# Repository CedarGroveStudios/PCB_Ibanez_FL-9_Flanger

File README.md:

## PCB_Ibanez_FL-9_Flanger
 An as-built schematic, PCB layout, and service guide to help with the repair of the Ibanez FL-9 Flanger guitar pedal.
 
 [FL9 Flanger Repair Blog (.pdf)](https://github.com/CedarGroveStudios/PCB_Ibanez_FL-9_Flanger/blob/main/docs/repair_blog/Ibanez_FL9_Flanger_Repair_Blog.pdf)

 [New Service Guide (Adafruit Learning System)](https://learn.adafruit.com/u/CGrover/pages/ibanez-fl9-service-guide)

 [New Service Guide (.pdf)](https://github.com/CedarGroveStudios/PCB_Ibanez_FL-9_Flanger/blob/main/docs/new_service_guide/Ibanez_FL9_Service_Guide.pdf)
 
 [KiCAD PCB Design Folder](https://github.com/CedarGroveStudios/PCB_Ibanez_FL-9_Flanger/tree/main/PCB)

 NOTE: The reverse-engineered PCB design was only used for relative component location -- the design is untested.

A thank you to [Mystic Effects Co](https://mysticeffectsco.com) for a helpful and inspiring FL9 capacitor replacement blog post. Also to Panasonic for continuing to maintain on-line datasheets for the bucket-brigade delay and clock driver chip set. Let's not forget how great it is that DigiKey still stocks fresh through-hole capacitors in their produce aisle.

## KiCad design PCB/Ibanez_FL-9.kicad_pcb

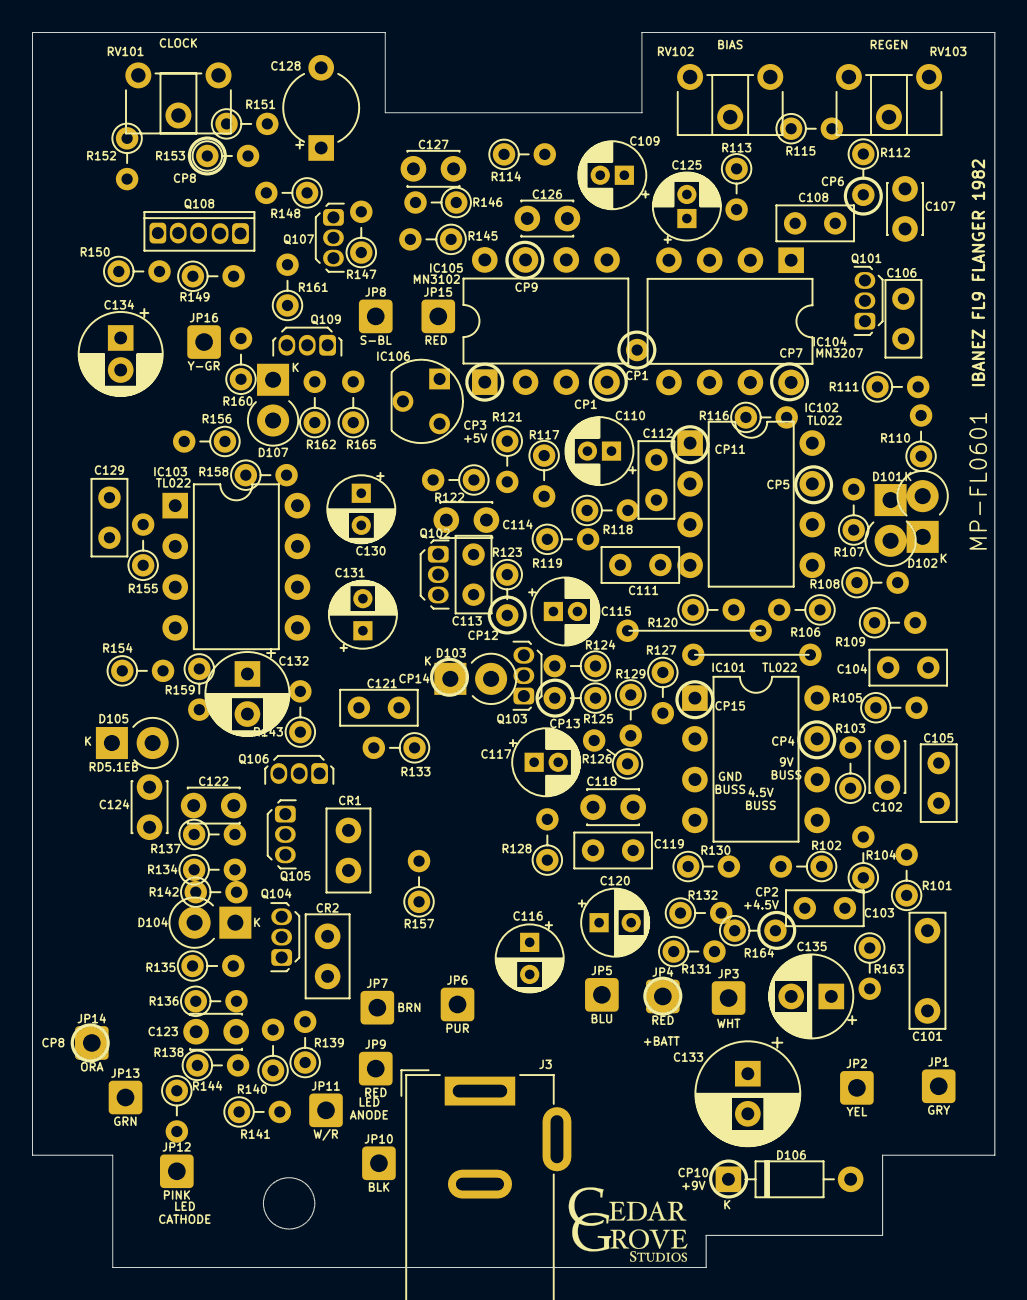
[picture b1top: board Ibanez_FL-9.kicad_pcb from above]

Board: 2 copper layers, 60.0 x 77.0 mm, 144 parts (0 on the bottom side), 77 nets, no tracks yet.

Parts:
C101: 0.047uf FILM; C_Rect_L7.0mm_W2.0mm_P5.00mm
C102, C118: 100pf CER; C_Disc_D3.0mm_W2.0mm_P2.50mm
C103: 0.022uf FILM; C_Rect_L4.6mm_W2.0mm_P2.50mm_MKS02_FKP02
C104, C121: 0.047uf FILM; C_Rect_L4.6mm_W2.0mm_P2.50mm_MKS02_FKP02
C105: 0.004uf FILM; C_Rect_L4.6mm_W2.0mm_P2.50mm_MKS02_FKP02
C106, C129: 0.01uf FILM; C_Rect_L4.6mm_W2.0mm_P2.50mm_MKS02_FKP02
C107: 120pf CER; C_Disc_D3.0mm_W2.0mm_P2.50mm
C108: 0.033uf FILM; C_Rect_L4.6mm_W2.0mm_P2.50mm_MKS02_FKP02
C109, C125: 1uf/50v; CP_Radial_D4.0mm_P1.50mm
C110, C115, C117: 1uf/50; CP_Radial_D4.0mm_P1.50mm
C111: 0.0015uf FILM; C_Rect_L4.6mm_W2.0mm_P2.50mm_MKS02_FKP02
C112: 0.001uf FILM; C_Rect_L4.6mm_W2.0mm_P2.50mm_MKS02_FKP02
C113: 0.003uf FILM; C_Rect_L4.6mm_W2.0mm_P2.50mm_MKS02_FKP02
C114: 560pf CER; C_Disc_D3.0mm_W2.0mm_P2.50mm
C116: 0.22uf/50v; CP_Radial_D4.0mm_P2.00mm
C119: 0.004 FILM; C_Rect_L4.6mm_W2.0mm_P2.50mm_MKS02_FKP02
C120: 10uf/16v; CP_Radial_D4.0mm_P2.00mm
C122, C123, C124: 1000pf CER; C_Disc_D3.0mm_W2.0mm_P2.50mm
C126: 20pf CER; C_Disc_D3.0mm_W2.0mm_P2.50mm
C127: 5pf CER; C_Disc_D3.0mm_W2.0mm_P2.50mm
C128: 22uf/10v TAN; CP_Radial_Tantal_D4.5mm_P5.00mm
C130, C131: 47uf/10v; CP_Radial_D4.0mm_P2.00mm
C132, C135: 47uf/6.3v; CP_Radial_D5.0mm_P2.50mm
C133: 100uf/16v; CP_Radial_D6.3mm_P2.50mm
C134: 100uf/10v; CP_Radial_D5.0mm_P2.00mm
CR1, CR2: CR_N01; C_Disc_D5.0mm_W2.5mm_P2.50mm
D101, D102, D103, D104, D107: 1N4148; D_T-1_P2.54mm_Vertical_KathodeUp
D105: RD5.1EB; D_T-1_P2.54mm_Vertical_KathodeUp
D106: W05C; D_DO-35_SOD27_P7.62mm_Horizontal
IC101, IC102, IC103: TL022; DIP-8_W7.62mm
IC104: MN3207; DIP-8_W7.62mm
IC105: MN3102; DIP-8_W7.62mm
IC106: LM78L05_TO92; TO-92
J3: EXT_DC; BarrelJack_Wuerth_6941xx301002
JP1: GRY; SolderWire-0.5sqmm_1x01_D0.9mm_OD2.1mm
JP2: YEL; SolderWire-0.5sqmm_1x01_D0.9mm_OD2.1mm
JP3: WHT; SolderWire-0.5sqmm_1x01_D0.9mm_OD2.1mm
JP4, JP9, JP15: RED; SolderWire-0.5sqmm_1x01_D0.9mm_OD2.1mm
JP5: BLU; SolderWire-0.5sqmm_1x01_D0.9mm_OD2.1mm
JP6: PUR; SolderWire-0.5sqmm_1x01_D0.9mm_OD2.1mm
JP7: BRN; SolderWire-0.5sqmm_1x01_D0.9mm_OD2.1mm
JP8: S-BL; SolderWire-0.5sqmm_1x01_D0.9mm_OD2.1mm
JP10: BLK; SolderWire-0.5sqmm_1x01_D0.9mm_OD2.1mm
JP11: W/R; SolderWire-0.5sqmm_1x01_D0.9mm_OD2.1mm
JP12: PINK; SolderWire-0.5sqmm_1x01_D0.9mm_OD2.1mm
JP13: GRN; SolderWire-0.5sqmm_1x01_D0.9mm_OD2.1mm
JP14: ORA; SolderWire-0.5sqmm_1x01_D0.9mm_OD2.1mm
JP16: Y-GR; SolderWire-0.5sqmm_1x01_D0.9mm_OD2.1mm
Q101, Q102, Q104, Q105, Q106, Q109: 2SC2458GR; TO-92Flat
Q103: 2SK44SPC; TO-92Flat
Q107: 2SA1048Y/GR; TO-92Flat
Q108: 2SC1583F; TO-92Flat_5-PIN
R101: 1K; R_Axial_DIN0204_L3.6mm_D1.6mm_P2.54mm_Vertical
R102, R106: 510K; R_Axial_DIN0204_L3.6mm_D1.6mm_P2.54mm_Vertical
R103, R127, R129: 91K; R_Axial_DIN0204_L3.6mm_D1.6mm_P2.54mm_Vertical
R104, R117, R118, R119, R128: 18K; R_Axial_DIN0204_L3.6mm_D1.6mm_P2.54mm_Vertical
R105: 180K; R_Axial_DIN0204_L3.6mm_D1.6mm_P2.54mm_Vertical
R107, R113, R124, R125, R132, R154, R161: 100K; R_Axial_DIN0204_L3.6mm_D1.6mm_P2.54mm_Vertical
R108, R112, R120, R123, R130, R134, R135, R148, R158, R159, R163, R164: 10K; R_Axial_DIN0204_L3.6mm_D1.6mm_P2.54mm_Vertical
R109: 47K; R_Axial_DIN0204_L3.6mm_D1.6mm_P2.54mm_Vertical
R110, R111: 12K; R_Axial_DIN0204_L3.6mm_D1.6mm_P2.54mm_Vertical
R114, R115: 5.1K; R_Axial_DIN0204_L3.6mm_D1.6mm_P2.54mm_Vertical
R116, R136, R137: 56K; R_Axial_DIN0204_L3.6mm_D1.6mm_P2.54mm_Vertical
R121, R122: 13K; R_Axial_DIN0204_L3.6mm_D1.6mm_P2.54mm_Vertical
R126, R156: 51K; R_Axial_DIN0204_L3.6mm_D1.6mm_P2.54mm_Vertical
R131: 470; R_Axial_DIN0204_L3.6mm_D1.6mm_P2.54mm_Vertical
R133, R138, R143: 1M; R_Axial_DIN0204_L3.6mm_D1.6mm_P2.54mm_Vertical
R139, R155: 62K; R_Axial_DIN0204_L3.6mm_D1.6mm_P2.54mm_Vertical
R140: 22K; R_Axial_DIN0204_L3.6mm_D1.6mm_P2.54mm_Vertical
R141: 22; R_Axial_DIN0204_L3.6mm_D1.6mm_P2.54mm_Vertical
R142: 100; R_Axial_DIN0204_L3.6mm_D1.6mm_P2.54mm_Vertical
R144: 2.2K; R_Axial_DIN0204_L3.6mm_D1.6mm_P2.54mm_Vertical
R145: 330; R_Axial_DIN0204_L3.6mm_D1.6mm_P2.54mm_Vertical
R146: 33K; R_Axial_DIN0204_L3.6mm_D1.6mm_P2.54mm_Vertical
R147: 27K; R_Axial_DIN0204_L3.6mm_D1.6mm_P2.54mm_Vertical
R149: 9.1K; R_Axial_DIN0204_L3.6mm_D1.6mm_P2.54mm_Vertical
R150: 2.2M; R_Axial_DIN0204_L3.6mm_D1.6mm_P2.54mm_Vertical
R151: 150K; R_Axial_DIN0204_L3.6mm_D1.6mm_P2.54mm_Vertical
R152: 220K; R_Axial_DIN0204_L3.6mm_D1.6mm_P2.54mm_Vertical
R153: 200K; R_Axial_DIN0204_L3.6mm_D1.6mm_P2.54mm_Vertical
R157: 1.2K; R_Axial_DIN0204_L3.6mm_D1.6mm_P2.54mm_Vertical
R160: 110K; R_Axial_DIN0204_L3.6mm_D1.6mm_P2.54mm_Vertical
R162: 270K; R_Axial_DIN0204_L3.6mm_D1.6mm_P2.54mm_Vertical
R165: 4.7K; R_Axial_DIN0204_L3.6mm_D1.6mm_P2.54mm_Vertical
RV101: 20K; Potentiometer_ACP_CA6-H2,5_Horizontal
RV102: 10K; Potentiometer_ACP_CA6-H2,5_Horizontal
RV103: 100K; Potentiometer_ACP_CA6-H2,5_Horizontal

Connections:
+5V: C134.1, IC103.8 (V+), IC104.5 (VDD), IC105.1 (VDD), IC106.1 (VO), Q107.1 (E), Q109.2 (C), R114.1, R147.1, R150.2, R152.2, R158.2, R161.2
+9V: C133.1, D106.1 (K), IC101.8 (V+), IC102.8 (V+), IC106.3 (VI), J3.2, R134.1, R135.1, R139.2, R163.1
/4.5v: C105.1, C135.1, Q101.2 (C), Q102.2 (C), R102.2, R106.2, R120.2, R124.1, R125.1, R130.2, R163.2, R164.2
/CP1: IC104.6 (CP2), IC105.4 (CP2)
/CP4: C102.2, IC101.7, R103.2, R105.1, R127.1
/CP5: D101.1 (K), D102.2 (A), IC102.7, R107.2, R110.1
/CP6: C106.2, C108.1, Q101.3 (E), R112.2
/CP7: C110.1, IC104.7 (OUT1), IC104.8 (OUT2), R116.1
/CP9: C126.2, IC105.7 (OX1), R145.1
/CP11: C112.2, IC102.1, R119.1, R121.2
/CP12: C113.2, C115.1, Q102.3 (E), R123.2
/CP13: C116.1, C117.1, Q103.1 (S), R125.2
/CP14: C121.2, D103.1 (K), R133.1
/CP15: C118.2, C119.2, C120.1, IC101.1, R129.2
GND: C107.1, C109.2, C111.1, C114.1, C121.1, C124.1, C125.2, C128.2, C132.2, C133.2, C134.2, C135.2, D106.2 (A), D107.2 (A), IC101.4 (V-), IC102.4 (V-), IC103.4 (V-), IC104.1 (GND), IC105.3 (GND), IC106.2 (GND), J3.1, Q108.3 (E), R112.1, R115.2, R116.2, R123.1, R132.1, R136.1, R137.1, R140.2, R142.1, R159.2, R162.1, R164.1, R165.1, RV101.1
unnamed: C101.2, R101.1
unnamed: C102.1, IC101.6 (-), R103.1, R104.2
unnamed: C103.1, RV103.2, RV103.3
unnamed: C104.1, R105.2
unnamed: C104.2, IC102.6 (-), R107.1, R108.1, R109.1
unnamed: C105.2, R104.1
unnamed: C106.1, R110.2, R111.2
unnamed: C107.2, Q101.1 (B), R111.1
unnamed: C108.2, IC104.3 (IN), R113.2
unnamed: C109.1, R113.1, RV102.2
unnamed: C110.2, R117.1
unnamed: C111.2, R117.2, R118.1, R119.2
unnamed: C112.1, IC102.2 (-), R118.2
unnamed: C113.1, R121.1, R122.1
unnamed: C114.2, Q102.1 (B), R122.2
unnamed: C115.2, Q103.3 (D), R124.2
unnamed: C116.2, JP5.1 (A)
unnamed: C117.2, R126.2
unnamed: C118.1, IC101.2 (-), R126.1, R127.2, R128.2, R129.1
unnamed: C119.1, R128.1
unnamed: C120.2, R131.1
unnamed: C122.1, C123.1, C124.2, R138.2, R141.1
unnamed: C122.2, CR1.1, Q105.1 (B), R137.2
unnamed: C123.2, CR2.2, Q104.1 (B), R136.2
unnamed: C125.1, IC104.4 (VGG), IC105.8 (VGG)
unnamed: C126.1, C127.1, IC105.5 (OX3), R146.1
unnamed: C127.2, Q107.3 (B), R146.2, R147.2
unnamed: C128.1, Q108.5 (B2), R149.2, R151.2, R153.2
unnamed: C129.1, IC103.2 (-), R154.1
unnamed: C129.2, IC103.1, R155.2
unnamed: C130.1, IC103.7, R156.1
unnamed: C130.2, C131.2
unnamed: C131.1, IC103.6 (-), R157.1
unnamed: C132.1, IC103.5 (+), R154.2, R158.1, R159.1
unnamed: CR1.2, Q104.2 (C), R135.2
unnamed: CR2.1, Q105.2 (C), R133.2, R134.2, R143.2
unnamed: D101.2 (A), D102.1 (K), R108.2
unnamed: D103.2 (A), Q103.2 (G)
unnamed: D104.1 (K), R142.2
unnamed: D104.2 (A), Q104.3 (E), Q105.3 (E), Q106.3 (E)
unnamed: D105.2 (A), R144.1
unnamed: D107.1 (K), Q109.1 (B), R160.1, R161.1, R162.2
unnamed: IC101.3 (+), R130.1
unnamed: IC101.5 (+), R101.2, R102.1
unnamed: IC102.3 (+), R120.1
unnamed: IC102.5 (+), R106.1
unnamed: IC103.3 (+), R155.1, R156.2
unnamed: IC104.2 (CP1), IC105.2 (CP1)
unnamed: JP3.1 (A), R131.2, R132.2
unnamed: Q109.3 (E), R165.2
unnamed: JP11.1 (A), R141.2
unnamed: Q106.1 (B), R143.1
unnamed: Q106.2 (C), R144.2
unnamed: Q107.2 (C), R145.2, R148.1
unnamed: Q108.1 (B1), Q108.2 (C1), R149.1, R150.1
unnamed: Q108.4 (C2), R148.2
unnamed: R109.2, RV103.1
unnamed: R114.2, RV102.1
unnamed: R115.1, RV102.3
unnamed: R138.1, R139.1, R140.1
unnamed: R151.1, RV101.2
unnamed: R152.1, RV101.3

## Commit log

2022-11-21 initial repo load
2022-11-21 update docs
2022-11-21 update docs; add BOM
2022-11-21 update docs; correct component labels and footprints
2022-11-22 update pcb layout
2022-11-23 update pcb design
2022-11-23 pcb layout v1.0
2022-11-23 add pcb 3d renders
2022-11-23 add custom components; fix all labels
2022-11-23 create test point overlay composite image
2022-11-23 update test points; add hybrid devices
2022-11-24 update service guide
2022-11-25 update board layout and docs
2022-11-26 update guide
2022-11-27 update schematic, guide, and docs
2022-11-28 update original pcb date
2022-11-30 update PCB and docs
2022-12-03 update graphics and waveforms; publish final version of guide
2022-12-03 update docs; add PCB design warning
2022-12-03 update docs; add reverse-engineered PCB functionality warning
2022-12-04 update testpoints on bot silk; fix spelling
2022-12-04 add appreciation
2022-12-05 update testpoint locator template
2022-12-05 add social photo
2022-12-15 update backup
2022-12-16 rename photos to prep for doc upgrade
2022-12-19 ignore .pages files
2022-12-20 archive original readme.md
2022-12-20 update docs; include service blog
2022-12-21 update trace enhanced photo
2022-12-22 reduce resolution to medium
2023-01-06 begin process to add hand-drawn traces
2023-01-06 revert to previous version
2023-01-06 add clean bottom traces image
2023-01-06 update jumper and CP1
2023-01-06 add hand-drawn PCB
2023-01-07 update hand-drawn PCB design
2023-01-07 add hand-drawn PCB design
2023-01-07 correct layout error and update docs
2023-01-07 add composite layout for learning guide
2023-01-07 move hand-drawn PCB design to private repo
2023-02-17 Update learning guide link.
2023-07-30 correct spelling
